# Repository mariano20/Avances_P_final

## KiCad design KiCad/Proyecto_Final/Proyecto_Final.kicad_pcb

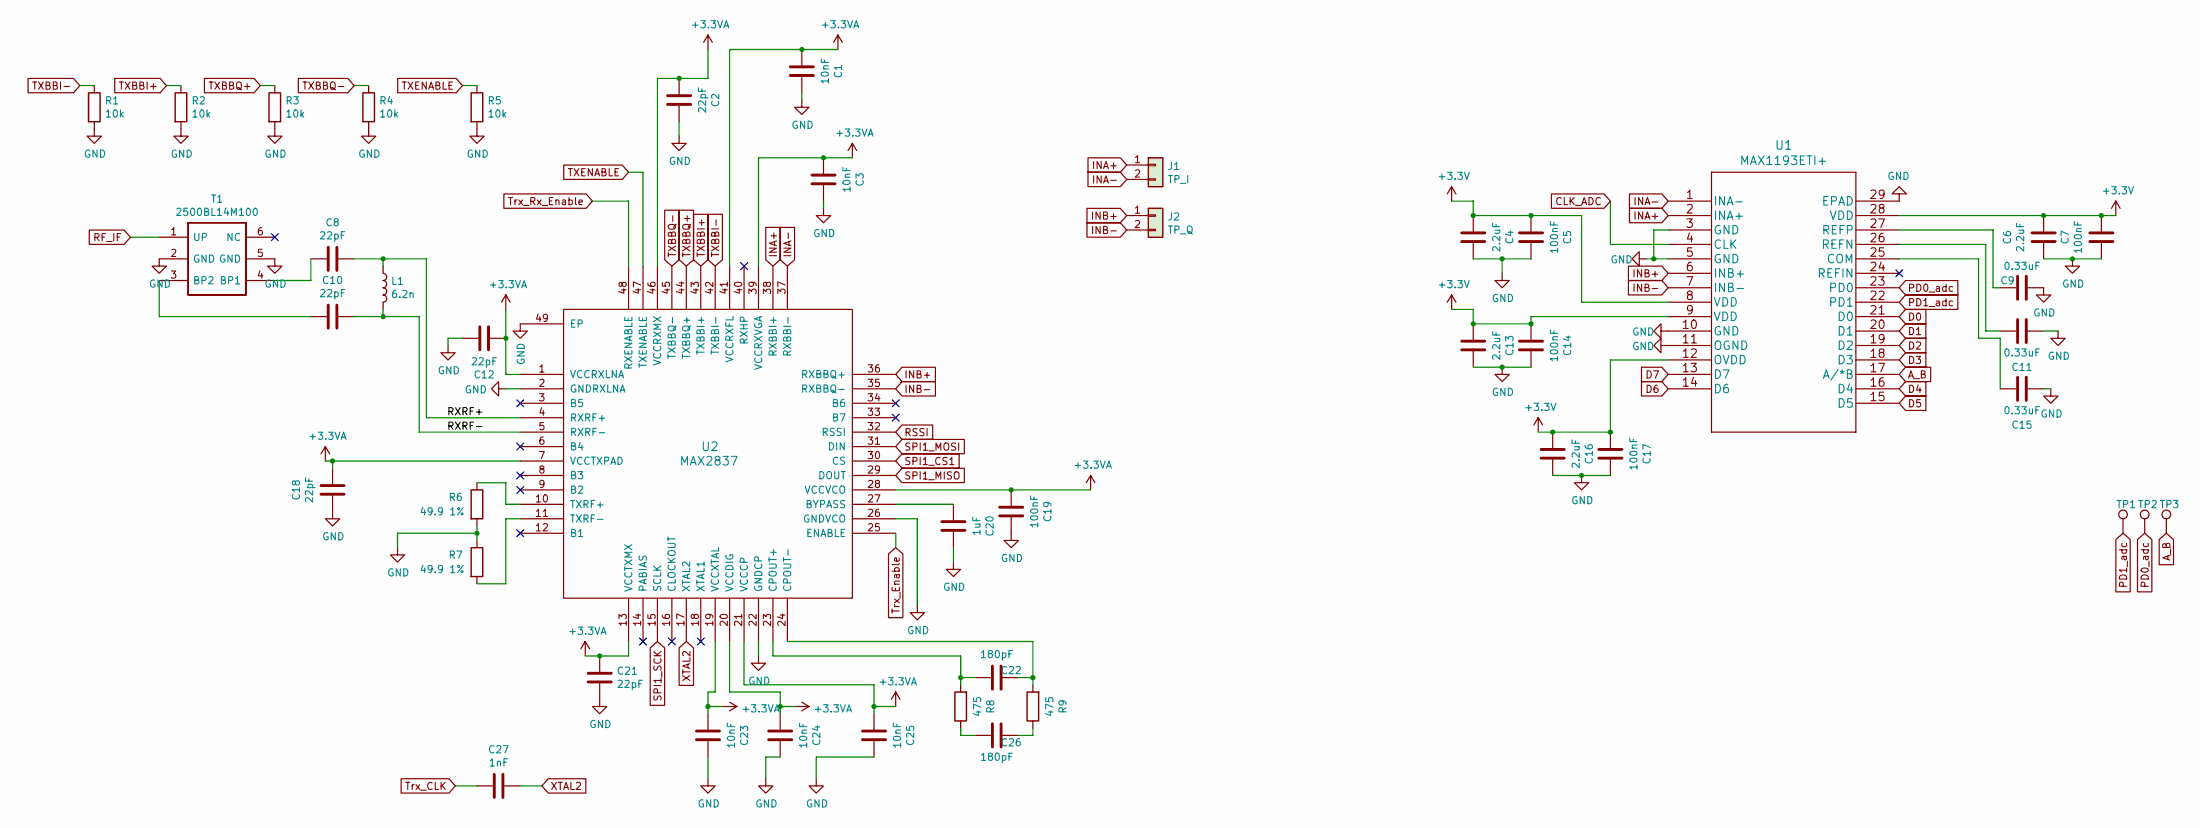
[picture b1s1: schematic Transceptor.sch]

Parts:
C1, C3, C23, C24, C25: 10nF; C_0402_1005Metric
C2, C8, C10, C12, C18, C21: 22pF; C_0402_1005Metric
C4: 2.2uF; C_0603_1608Metric
C5, C7, C14, C17, C19: 100nF; C_0402_1005Metric
C6, C13, C16: 2.2uF; C_0805_2012Metric
C9, C11, C15: 0.33uF; C_0603_1608Metric
C20: 1uF; C_0805_2012Metric
C22, C26: 180pF; C_0402_1005Metric
C27: 1nF; C_0402_1005Metric
J1: TP_I; PinHeader_1x02_P1.27mm_Vertical
J2: TP_Q; PinHeader_1x02_P1.27mm_Vertical
L1: 6.2n; L_0402_1005Metric
R1, R2, R3, R4, R5: 10k; R_0402_1005Metric
R6, R7: 49.9 1%; R_0402_1005Metric
R8, R9: 475; R_0402_1005Metric
T1: 2500BL14M100; Balun_Johanson_1.6x0.8mm; Manufacturer_Part_Number 2500BL14M100T; Mouser Part Number 609-2500BL14M100T
TP1, TP2, TP3: TestPoint; TestPoint_Mask_D0.4mm
U1: MAX1193ETI+; MAX1193ETI&plus_T
U2: MAX2837; MAX2837ETM&plus_

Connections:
+3.3VA: C1.2, C2.2, C3.2, C12.2, C18.1, C19.2, C21.1, C23.2, C24.2, C25.2, U2.1 (VCCRXLNA), U2.7 (VCCTXPAD), U2.13 (VCCTXMX), U2.19 (VCCXTAL), U2.20 (VCCDIG), U2.21 (VCCCP), U2.28 (VCCVCO), U2.39 (VCCRXVGA), U2.41 (VCCRXFL), U2.46 (VCCRXMX); also elsewhere on the board
+3V3: C4.2, C5.2, C6.1, C7.1, C13.2, C14.2, C16.2, C17.2, U1.8 (VDD), U1.9 (VDD), U1.12 (OVDD), U1.28 (VDD); also elsewhere on the board
/Transceptor/RXRF+: C8.1, L1.1, U2.4 (RXRF+)
/Transceptor/RXRF-: C10.1, L1.2, U2.5 (RXRF-)
A_B: TP3.1, U1.17 (A/*B); also elsewhere on the board
CLK_ADC: U1.4 (CLK); also elsewhere on the board
D0: U1.21 (D0); also elsewhere on the board
D1: U1.20 (D1); also elsewhere on the board
D2: U1.19 (D2); also elsewhere on the board
D3: U1.18 (D3); also elsewhere on the board
D4: U1.16 (D4); also elsewhere on the board
D5: U1.15 (D5); also elsewhere on the board
D6: U1.14 (D6); also elsewhere on the board
D7: U1.13 (D7); also elsewhere on the board
GND: C1.1, C2.1, C3.1, C4.1, C5.1, C6.2, C7.2, C9.2, C11.1, C12.1, C13.1, C14.1, C15.1, C16.1, C17.1, C18.2, C19.1, C20.1, C21.2, C23.1, C24.1, C25.1, R1.2, R2.2, R3.2, R4.2, R5.2, R6.2, R7.1, T1.2 (GND), T1.5 (GND), U1.3 (GND), U1.5 (GND), U1.10 (GND), U1.11 (OGND), U1.29 (EPAD), U2.2 (GNDRXLNA), U2.22 (GNDCP), U2.26 (GNDVCO), U2.49 (EP); also elsewhere on the board
INA+: J1.1, U1.2 (INA+), U2.38 (RXBBI+)
INA-: J1.2, U1.1 (INA-), U2.37 (RXBBI-)
INB+: J2.1, U1.6 (INB+), U2.36 (RXBBQ+)
INB-: J2.2, U1.7 (INB-), U2.35 (RXBBQ-)
unnamed: C8.2, T1.4 (BP1)
unnamed: C9.1, U1.27 (REFP)
unnamed: C10.2, T1.3 (BP2)
unnamed: C11.2, U1.26 (REFN)
unnamed: C15.2, U1.25 (COM)
unnamed: C20.2, U2.27 (BYPASS)
unnamed: C22.1, R9.2, U2.24 (CPOUT-)
unnamed: C22.2, R8.2, U2.23 (CPOUT+)
unnamed: C26.1, R9.1
unnamed: C26.2, R8.1
unnamed: R6.1, U2.10 (TXRF+)
unnamed: R7.2, U2.11 (TXRF-)
PD0_adc: TP2.1, U1.23 (PD0); also elsewhere on the board
PD1_adc: TP1.1, U1.22 (PD1); also elsewhere on the board
RF_IF: T1.1 (UP); also elsewhere on the board
RSSI: U2.32 (RSSI); also elsewhere on the board
SPI1_CS1: U2.30 (CS); also elsewhere on the board
SPI1_MISO: U2.29 (DOUT); also elsewhere on the board
SPI1_MOSI: U2.31 (DIN); also elsewhere on the board
SPI1_SCK: U2.15 (SCLK); also elsewhere on the board
TXBBI+: R2.1, U2.43 (TXBBI+)
TXBBI-: R1.1, U2.42 (TXBBI-)
TXBBQ+: R3.1, U2.44 (TXBBQ+)
TXBBQ-: R4.1, U2.45 (TXBBQ-)
TXENABLE: R5.1, U2.47 (TXENABLE)
Trx_CLK: C27.2; also elsewhere on the board
Trx_Enable: U2.25 (ENABLE); also elsewhere on the board
Trx_Rx_Enable: U2.48 (RXENABLE); also elsewhere on the board
XTAL2: C27.1, U2.17 (XTAL2)

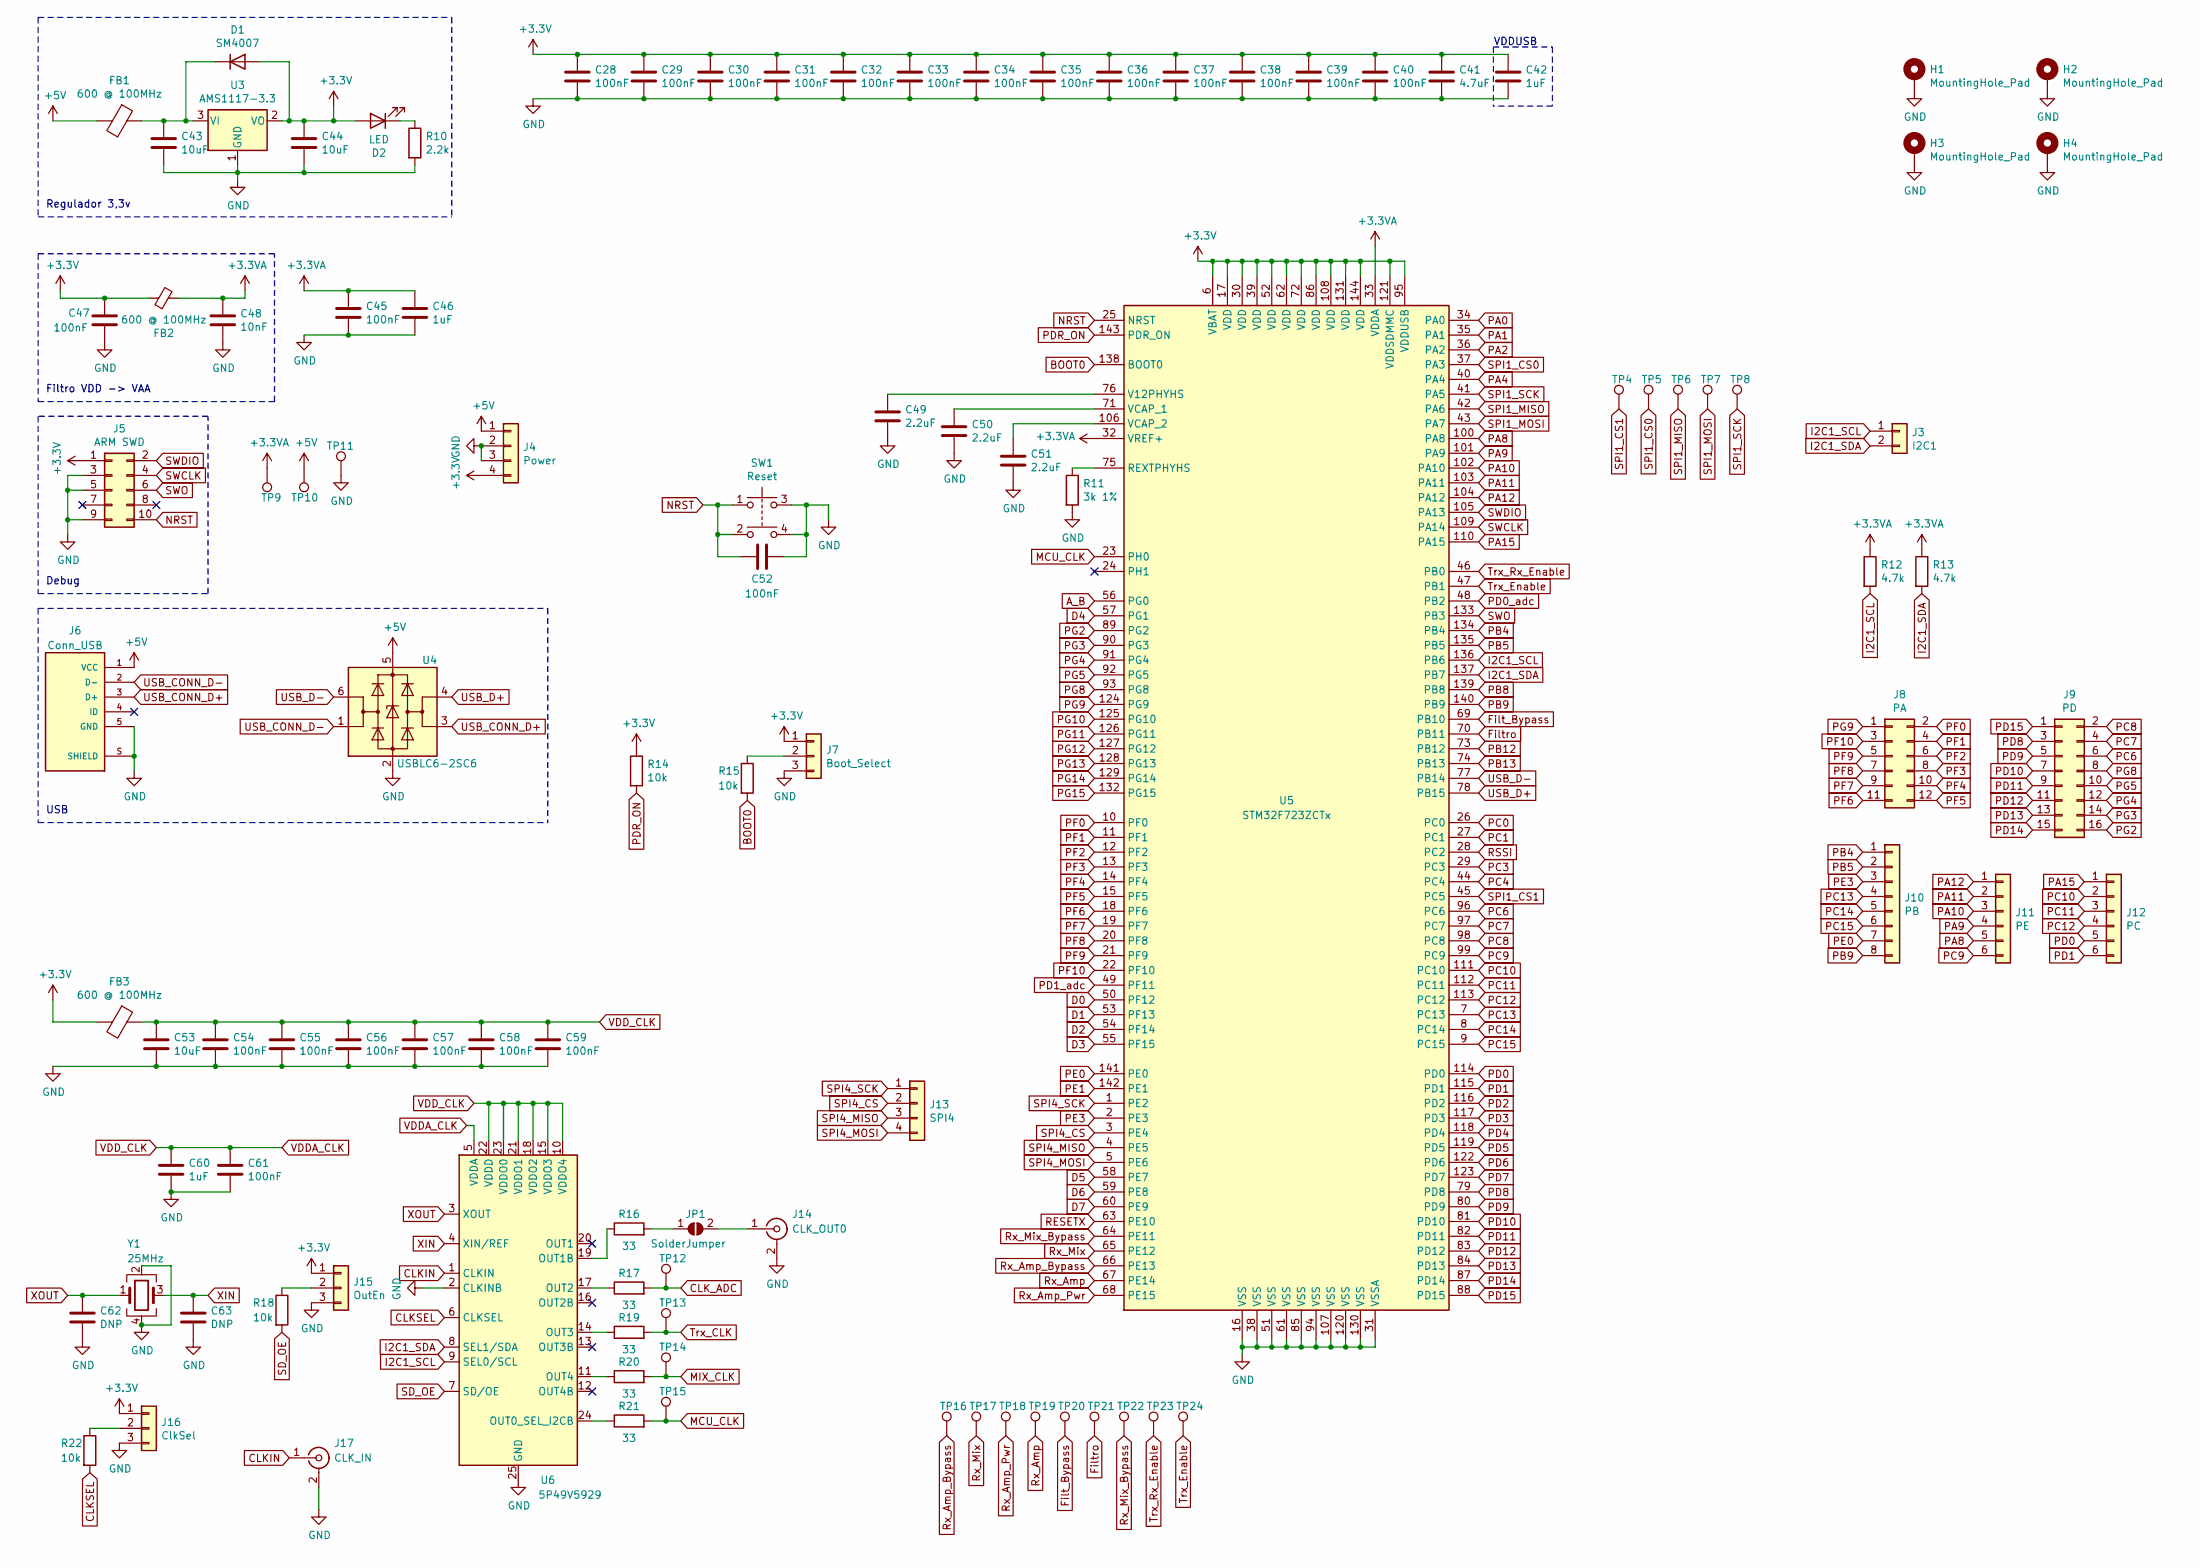
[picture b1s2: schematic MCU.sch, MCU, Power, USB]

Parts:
C28, C29, C30, C31, C32, C33, C34, C35, C36, C37, C38, C39, C40, C45, C47, C52, C54, C55, C56, C57, C58, C59, C61: 100nF; C_0402_1005Metric
C41: 4.7uF; C_0805_2012Metric
C42, C46, C60: 1uF; C_0805_2012Metric
C43, C44, C53: 10uF; C_0805_2012Metric
C48: 10nF; C_0402_1005Metric
C49, C50, C51: 2.2uF; C_0805_2012Metric
C62, C63: DNP; C_0402_1005Metric
D1: SM4007; D_SOD-123F
D2: LED; LED_0603_1608Metric
FB1, FB2, FB3: 600 @ 100MHz; L_0402_1005Metric
H1, H2, H3, H4: MountingHole_Pad; MountingHole_3.2mm_M3_Pad_Via
J3: I2C1; PinHeader_2x01_P2.54mm_Vertical
J4: Power; PinHeader_1x04_P2.54mm_Vertical
J5: ARM SWD; PinHeader_2x05_P2.54mm_Vertical_SMD
J6: Conn_USB; CUI_UJ2-MIBH-G-SMT-TR; PARTREV 1.0
J7: Boot_Select; PinHeader_1x03_P2.54mm_Vertical
J8: PA; PinHeader_2x06_P2.54mm_Vertical
J9: PD; PinHeader_2x08_P2.54mm_Vertical
J10: PB; PinHeader_1x08_P2.54mm_Vertical
J11: PE; PinHeader_1x06_P2.54mm_Vertical
J12: PC; PinHeader_1x06_P2.54mm_Vertical
J13: SPI4; PinHeader_1x04_P2.54mm_Vertical
J14: CLK_OUT0; RFSOLUTIONS_CON-SMA-EDGE-S
J15: OutEn; PinHeader_1x03_P2.54mm_Vertical
J16: ClkSel; PinHeader_1x03_P2.54mm_Vertical
J17: CLK_IN; RFSOLUTIONS_CON-SMA-EDGE-S
JP1: SolderJumper; SolderJumper-2_P1.3mm_Open_RoundedPad1.0x1.5mm
R10: 2.2k; R_0402_1005Metric
R11: 3k 1%; R_0402_1005Metric
R12, R13: 4.7k; R_0402_1005Metric
R14, R15, R18, R22: 10k; R_0402_1005Metric
R16, R17, R19, R20, R21: 33; R_0402_1005Metric
SW1: Reset; PTS647SN50SMTR2LFS
TP4, TP5, TP6, TP7, TP8, TP9, TP10, TP12, TP13, TP14, TP15, TP16, TP17, TP18, TP19, TP20, TP21, TP22, TP23, TP24: TestPoint; TestPoint_Pad_D1.0mm_NoRef
TP11: TestPoint; TestPoint_Pad_1.5x1.5mm
U3: AMS1117-3.3; SOT-223-3_TabPin2
U4: USBLC6-2SC6; SOT-23-6
U5: STM32F723ZCTx; LQFP-144_20x20mm_P0.5mm
U6: 5P49V5929; QFN-24-1EP_4x4mm_P0.5mm_EP2.8x2.8mm
Y1: 25MHz; Crystal_SMD_EuroQuartz_MT-4Pin_3.2x2.5mm

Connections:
+3.3VA: C45.1, C46.1, C48.1, FB2.2, R12.1, R13.1, TP9.1, U5.32 (VREF+), U5.33 (VDDA); also elsewhere on the board
+3V3: C28.1, C29.1, C30.1, C31.1, C32.1, C33.1, C34.1, C35.1, C36.1, C37.1, C38.1, C39.1, C40.1, C41.1, C42.1, C44.1, C47.1, D1.2 (A), D2.2 (A), FB2.1, FB3.2, J4.4, J5.1, J7.1, J15.1, J16.1, R14.1, U3.2 (VO), U5.6 (VBAT), U5.17 (VDD), U5.30 (VDD), U5.39 (VDD), U5.52 (VDD), U5.62 (VDD), U5.72 (VDD), U5.86 (VDD), U5.95 (VDDUSB), U5.108 (VDD), U5.121 (VDDSDMMC), U5.131 (VDD), U5.144 (VDD); also elsewhere on the board
+5V: FB1.2, J4.1, J6.1 (VCC), TP10.1, U4.5 (VBUS)
A_B: U5.56 (PG0); also elsewhere on the board
BOOT0: R15.2, U5.138 (BOOT0)
CLKIN: J17.1 (In), U6.1 (CLKIN)
CLKSEL: R22.2, U6.6 (CLKSEL)
CLK_ADC: R17.2, TP12.1; also elsewhere on the board
D0: U5.50 (PF12); also elsewhere on the board
D1: U5.53 (PF13); also elsewhere on the board
D2: U5.54 (PF14); also elsewhere on the board
D3: U5.55 (PF15); also elsewhere on the board
D4: U5.57 (PG1); also elsewhere on the board
D5: U5.58 (PE7); also elsewhere on the board
D6: U5.59 (PE8); also elsewhere on the board
D7: U5.60 (PE9); also elsewhere on the board
Filt_Bypass: TP20.1, U5.69 (PB10); also elsewhere on the board
Filtro: TP21.1, U5.70 (PB11); also elsewhere on the board
GND: C28.2, C29.2, C30.2, C31.2, C32.2, C33.2, C34.2, C35.2, C36.2, C37.2, C38.2, C39.2, C40.2, C41.2, C42.2, C43.2, C44.2, C45.2, C46.2, C47.2, C48.2, C49.2, C50.2, C51.2, C52.1, C53.2, C54.2, C55.2, C56.2, C57.2, C58.2, C59.2, C60.2, C61.2, C62.2, C63.2, H1.1, H2.1, H3.1, H4.1, J4.2, J4.3, J5.3, J5.5, J5.9, J6.5 (GND), J6.S (SHIELD), J7.3, J14.2 (Ext), J15.3, J16.3, J17.2 (Ext), R10.2, R11.2, SW1.3, SW1.4, TP11.1, U3.1 (GND), U4.2 (GND), U5.16 (VSS), U5.31 (VSSA), U5.38 (VSS), U5.51 (VSS), U5.61 (VSS), U5.85 (VSS), U5.94 (VSS), U5.107 (VSS), U5.120 (VSS), U5.130 (VSS), U6.2 (CLKINB), U6.25 (GND), Y1.2, Y1.4; also elsewhere on the board
I2C1_SCL: J3.1, R12.2, U5.136 (PB6), U6.9 (SEL0/SCL)
I2C1_SDA: J3.2, R13.2, U5.137 (PB7), U6.8 (SEL1/SDA)
MCU_CLK: R21.2, TP15.1, U5.23 (PH0)
MIX_CLK: R20.2, TP14.1; also elsewhere on the board
NRST: C52.2, J5.10, SW1.1, SW1.2, U5.25 (NRST)
unnamed: C43.1, D1.1 (K), FB1.1, U3.3 (VI)
unnamed: C49.1, U5.76 (V12PHYHS)
unnamed: C50.1, U5.71 (VCAP_1)
unnamed: C51.1, U5.106 (VCAP_2)
unnamed: D2.1 (K), R10.1
unnamed: J7.2, R15.1
unnamed: J14.1 (In), JP1.2 (B)
unnamed: J15.2, R18.1
unnamed: J16.2, R22.1
unnamed: JP1.1 (A), R16.2
unnamed: R11.1, U5.75 (REXTPHYHS)
unnamed: R16.1, U6.19 (OUT1B)
unnamed: R17.1, U6.17 (OUT2)
unnamed: R19.1, U6.14 (OUT3)
unnamed: R20.1, U6.11 (OUT4)
unnamed: R21.1, U6.24 (OUT0_SEL_I2CB)
PA0: U5.34 (PA0)
PA1: U5.35 (PA1)
PA2: U5.36 (PA2)
PA4: U5.40 (PA4)
PA8: J11.5, U5.100 (PA8)
PA9: J11.4, U5.101 (PA9)
PA10: J11.3, U5.102 (PA10)
PA11: J11.2, U5.103 (PA11)
PA12: J11.1, U5.104 (PA12)
PA15: J12.1, U5.110 (PA15)
PB4: J10.1, U5.134 (PB4)
PB5: J10.2, U5.135 (PB5)
PB8: U5.139 (PB8)
PB9: J10.8, U5.140 (PB9)
PB12: U5.73 (PB12)
PB13: U5.74 (PB13)
PC0: U5.26 (PC0)
PC1: U5.27 (PC1)
PC3: U5.29 (PC3)
PC4: U5.44 (PC4)
PC6: J9.6, U5.96 (PC6)
PC7: J9.4, U5.97 (PC7)
PC8: J9.2, U5.98 (PC8)
PC9: J11.6, U5.99 (PC9)
PC10: J12.2, U5.111 (PC10)
PC11: J12.3, U5.112 (PC11)
PC12: J12.4, U5.113 (PC12)
PC13: J10.4, U5.7 (PC13)
PC14: J10.5, U5.8 (PC14)
PC15: J10.6, U5.9 (PC15)
PD0: J12.5, U5.114 (PD0)
PD0_adc: U5.48 (PB2); also elsewhere on the board
PD1: J12.6, U5.115 (PD1)
PD1_adc: U5.49 (PF11); also elsewhere on the board
PD2: U5.116 (PD2)
PD3: U5.117 (PD3)
PD4: U5.118 (PD4)
PD5: U5.119 (PD5)
PD6: U5.122 (PD6)
PD7: U5.123 (PD7)
PD8: J9.3, U5.79 (PD8)
PD9: J9.5, U5.80 (PD9)
PD10: J9.7, U5.81 (PD10)
PD11: J9.9, U5.82 (PD11)
PD12: J9.11, U5.83 (PD12)
PD13: J9.13, U5.84 (PD13)
PD14: J9.15, U5.87 (PD14)
PD15: J9.1, U5.88 (PD15)
PDR_ON: R14.2, U5.143 (PDR_ON)
PE0: J10.7, U5.141 (PE0)
PE1: U5.142 (PE1)
PE3: J10.3, U5.2 (PE3)
PF0: J8.2, U5.10 (PF0)
PF1: J8.4, U5.11 (PF1)
PF2: J8.6, U5.12 (PF2)
PF3: J8.8, U5.13 (PF3)
PF4: J8.10, U5.14 (PF4)
PF5: J8.12, U5.15 (PF5)
PF6: J8.11, U5.18 (PF6)
PF7: J8.9, U5.19 (PF7)
PF8: J8.7, U5.20 (PF8)
PF9: J8.5, U5.21 (PF9)
PF10: J8.3, U5.22 (PF10)
PG2: J9.16, U5.89 (PG2)
PG3: J9.14, U5.90 (PG3)
PG4: J9.12, U5.91 (PG4)
PG5: J9.10, U5.92 (PG5)
PG8: J9.8, U5.93 (PG8)
PG9: J8.1, U5.124 (PG9)
PG10: U5.125 (PG10)
PG11: U5.126 (PG11)
PG12: U5.127 (PG12)
PG13: U5.128 (PG13)
PG14: U5.129 (PG14)
PG15: U5.132 (PG15)
RESETX: U5.63 (PE10); also elsewhere on the board
RSSI: U5.28 (PC2); also elsewhere on the board
Rx_Amp: TP19.1, U5.67 (PE14); also elsewhere on the board
Rx_Amp_Bypass: TP16.1, U5.66 (PE13); also elsewhere on the board
Rx_Amp_Pwr: TP18.1, U5.68 (PE15); also elsewhere on the board
Rx_Mix: TP17.1, U5.65 (PE12); also elsewhere on the board
Rx_Mix_Bypass: TP22.1, U5.64 (PE11); also elsewhere on the board
SD_OE: R18.2, U6.7 (SD/OE)
SPI1_CS0: TP5.1, U5.37 (PA3); also elsewhere on the board
SPI1_CS1: TP4.1, U5.45 (PC5); also elsewhere on the board
SPI1_MISO: TP6.1, U5.42 (PA6); also elsewhere on the board
SPI1_MOSI: TP7.1, U5.43 (PA7); also elsewhere on the board
SPI1_SCK: TP8.1, U5.41 (PA5); also elsewhere on the board
SPI4_CS: J13.2, U5.3 (PE4)
SPI4_MISO: J13.3, U5.4 (PE5)
SPI4_MOSI: J13.4, U5.5 (PE6)
SPI4_SCK: J13.1, U5.1 (PE2)
SWCLK: J5.4, U5.109 (PA14)
SWDIO: J5.2, U5.105 (PA13)
SWO: J5.6, U5.133 (PB3)
Trx_CLK: R19.2, TP13.1; also elsewhere on the board
Trx_Enable: TP24.1, U5.47 (PB1); also elsewhere on the board
Trx_Rx_Enable: TP23.1, U5.46 (PB0); also elsewhere on the board
USB_CONN_D+: J6.3 (D+), U4.3 (I/O2)
USB_CONN_D-: J6.2 (D-), U4.1 (I/O1)
USB_D+: U4.4 (I/O2), U5.78 (PB15)
USB_D-: U4.6 (I/O1), U5.77 (PB14)
VDDA_CLK: C53.1, C54.1, C55.1, C56.1, C57.1, C58.1, C59.1, C60.1, C61.1, FB3.1, U6.5 (VDDA), U6.10 (VDDO4), U6.15 (VDDO3), U6.18 (VDDO2), U6.21 (VDDO1), U6.22 (VDDD), U6.23 (VDDO0)
XIN: C63.1, U6.4 (XIN/REF), Y1.3
XOUT: C62.1, U6.3 (XOUT), Y1.1

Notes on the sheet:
Regulador 3,3v
Filtro VDD -> VAA
Debug
USB
VDDUSB

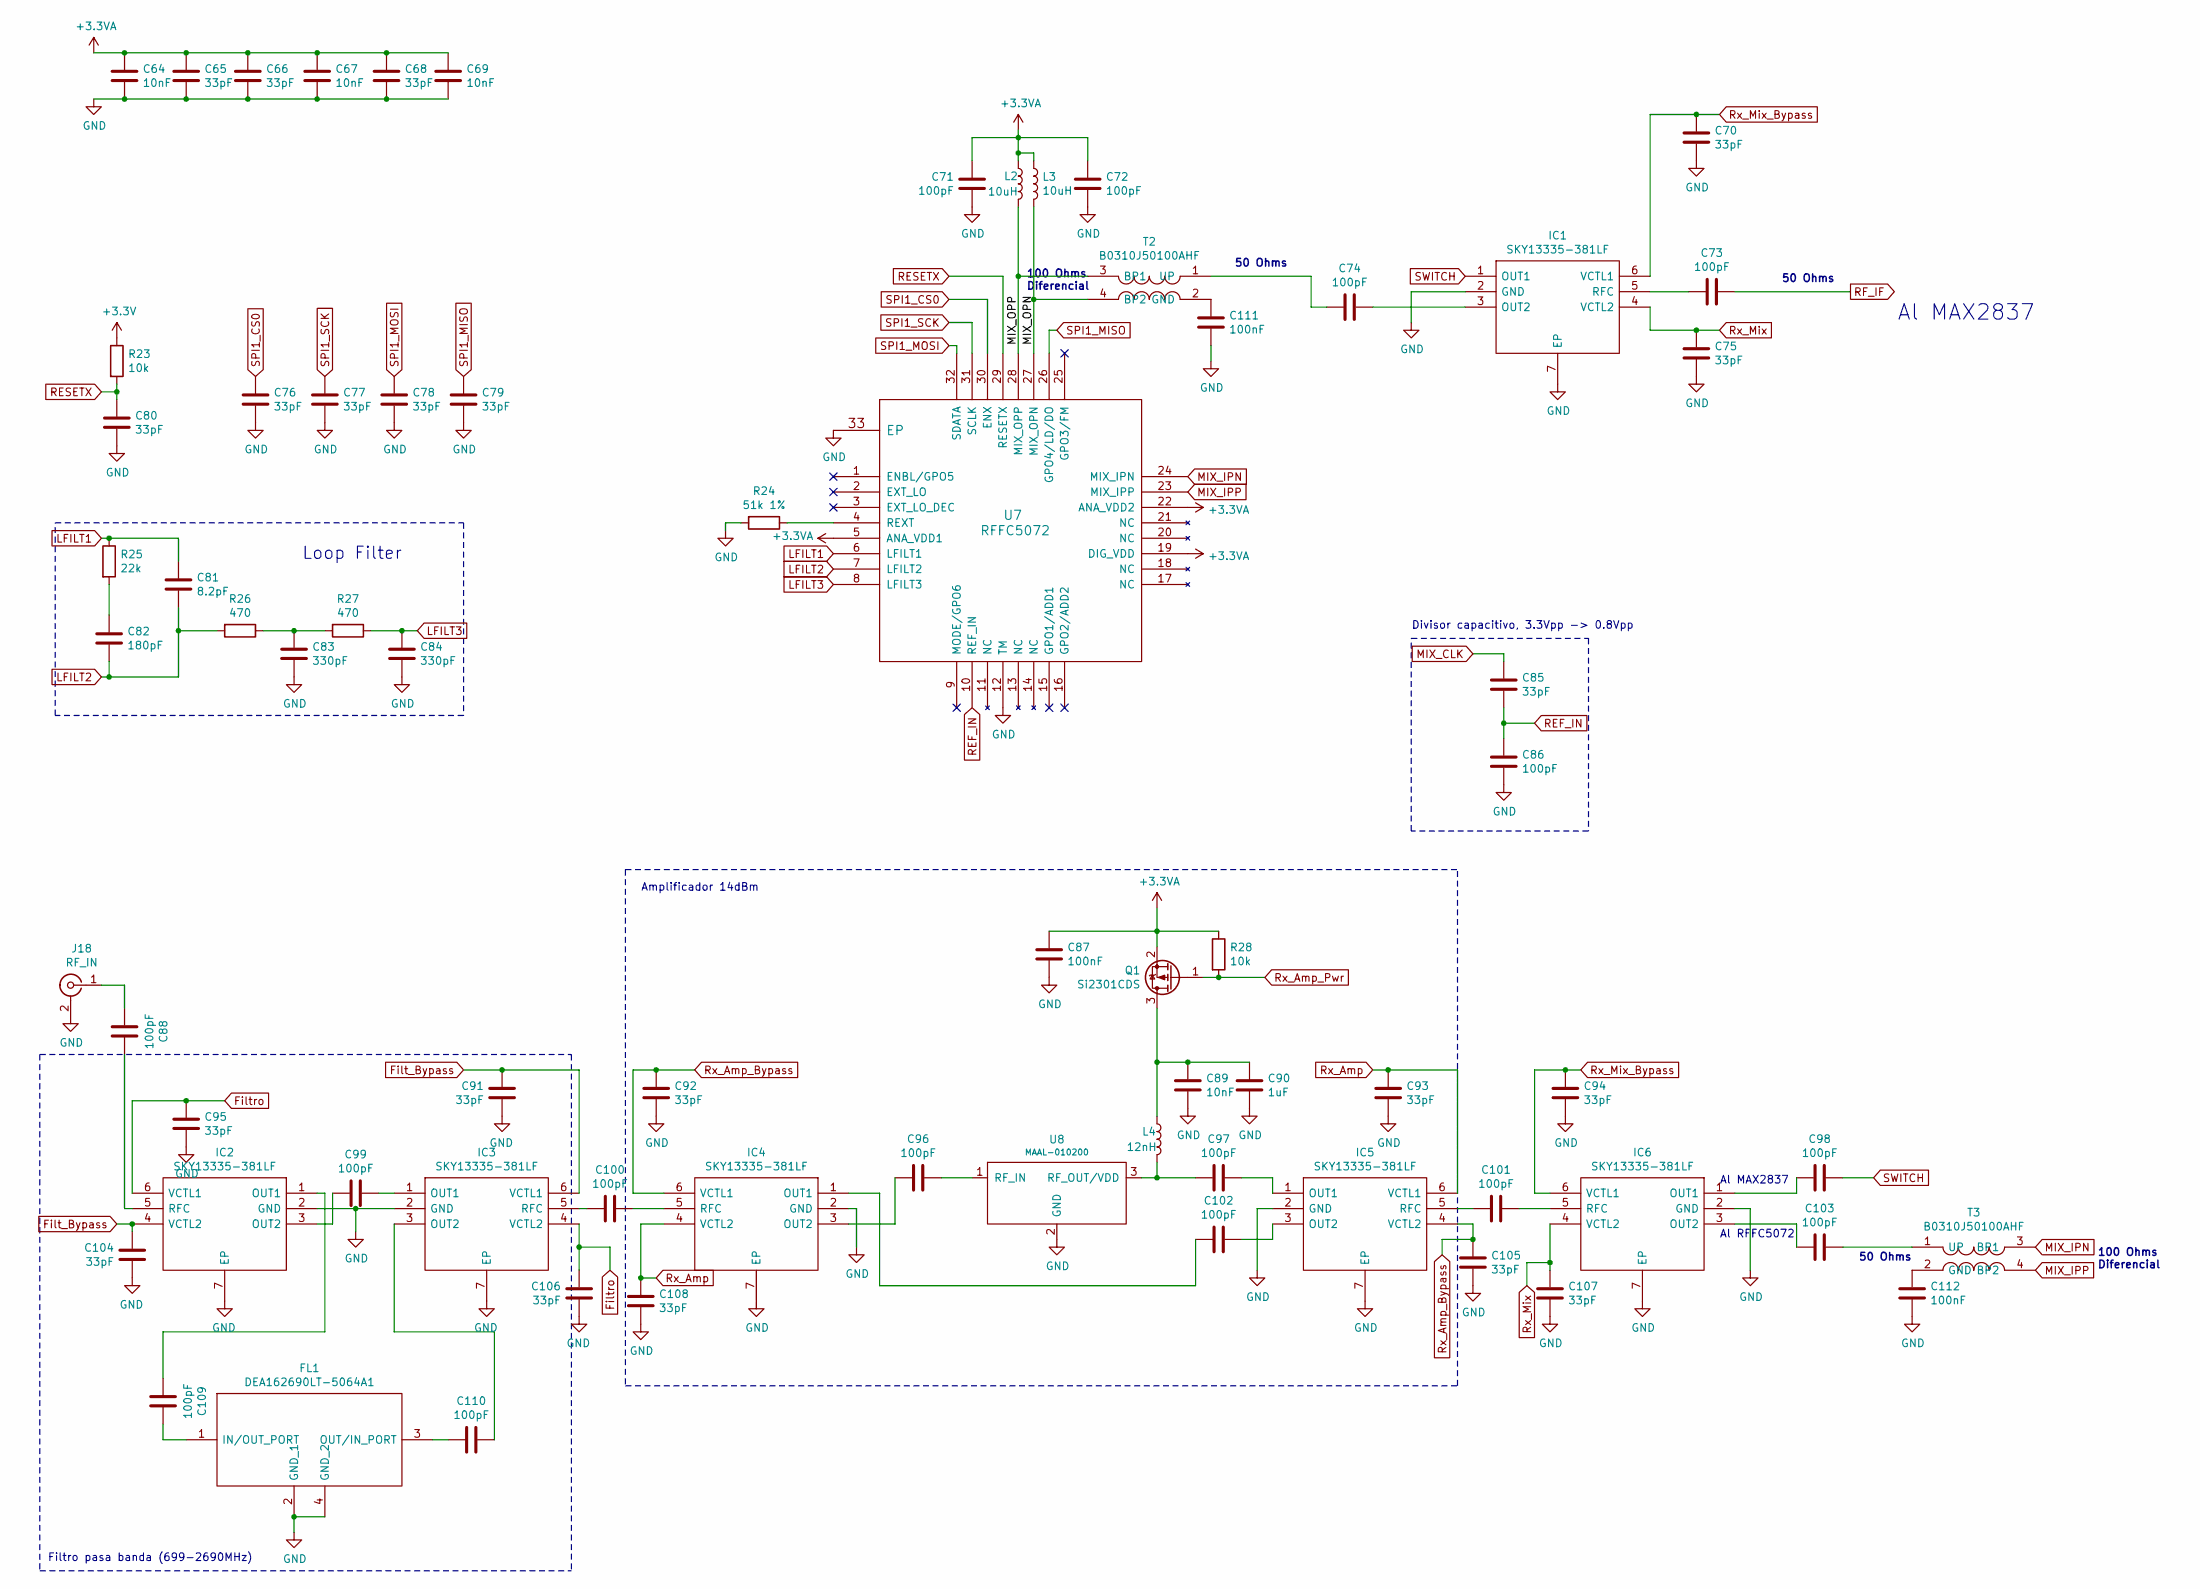
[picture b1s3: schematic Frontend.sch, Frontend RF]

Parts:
C64, C67, C69, C89: 10nF; C_0402_1005Metric
C65, C66, C68, C70, C75, C76, C77, C78, C79, C80, C85, C91, C92, C93, C94, C95, C104, C105, C106, C107, C108: 33pF; C_0402_1005Metric
C71, C72, C73, C74, C86, C88, C96, C97, C98, C99, C100, C101, C102, C103, C109, C110: 100pF; C_0402_1005Metric
C81: 8.2pF; C_0603_1608Metric
C82: 180pF; C_0201_0603Metric
C83, C84: 330pF; C_0402_1005Metric
C87, C111, C112: 100nF; C_0402_1005Metric
C90: 1uF; C_0402_1005Metric
FL1: DEA162690LT-5064A1; DEA162690LT5051B1; Manufacturer_Part_Number DEA162690LT-5064A1
IC1, IC2, IC3, IC4, IC5, IC6: SKY13335-381LF; SON50P200X150X50-7N; Mouser Part Number 873-SKY13335-381LF
J18: RF_IN; RFSOLUTIONS_CON-SMA-EDGE-S
L2, L3: 10uH; L_0805_2012Metric
L4: 12nH; L_0402_1005Metric
Q1: Si2301CDS; SOT-23
R23, R28: 10k; R_0402_1005Metric
R24: 51k 1%; R_0402_1005Metric
R25: 22k; R_0402_1005Metric
R26, R27: 470; R_0402_1005Metric
T2, T3: B0310J50100AHF; Manufacturer_Part_Number B0310J50100AHF; Mouser Part Number 620-B0310J50100AHF
U7: RFFC5072; QFN-32-1EP_5x5mm_P0.5mm_EP3.7x3.7mm
U8: MAAL-010200; SOT-89-3

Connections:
+3.3VA: C64.1, C65.1, C66.1, C67.1, C68.1, C69.1, C71.1, C72.1, C87.1, L2.1, L3.1, Q1.2 (S), R28.1, U7.5 (ANA_VDD1), U7.19 (DIG_VDD), U7.22 (ANA_VDD2); also elsewhere on the board
+3V3: R23.1; also elsewhere on the board
/Frontend_analog/MIX_OPN: L3.2, T2.4 (BP2), U7.27 (MIX_OPN)
/Frontend_analog/MIX_OPP: L2.2, T2.3 (BP1), U7.28 (MIX_OPP)
Filt_Bypass: C91.1, C104.1, IC2.4 (VCTL2), IC3.6 (VCTL1); also elsewhere on the board
Filtro: C95.1, C106.1, IC2.6 (VCTL1), IC3.4 (VCTL2); also elsewhere on the board
GND: C64.2, C65.2, C66.2, C67.2, C68.2, C69.2, C70.2, C71.2, C72.2, C75.2, C76.2, C77.2, C78.2, C79.2, C80.2, C83.2, C84.2, C86.2, C87.2, C89.2, C90.2, C91.2, C92.2, C93.2, C94.2, C95.2, C104.2, C105.2, C106.2, C107.2, C108.2, C111.2, C112.2, FL1.2 (GND_1), FL1.4 (GND_2), IC1.2 (GND), IC1.7 (EP), IC2.2 (GND), IC2.7 (EP), IC3.2 (GND), IC3.7 (EP), IC4.2 (GND), IC4.7 (EP), IC5.2 (GND), IC5.7 (EP), IC6.2 (GND), IC6.7 (EP), J18.2 (Ext), R24.2, U7.12 (TM), U7.33 (EP), U8.2 (GND); also elsewhere on the board
LFILT1: C81.1, R25.1, U7.6 (LFILT1)
LFILT2: C81.2, C82.2, R26.2, U7.7 (LFILT2)
LFILT3: C84.1, R27.1, U7.8 (LFILT3)
MIX_CLK: C85.1; also elsewhere on the board
MIX_IPN: T3.3 (BP1), U7.24 (MIX_IPN)
MIX_IPP: T3.4 (BP2), U7.23 (MIX_IPP)
unnamed: C73.2, IC1.5 (RFC)
unnamed: C74.1, IC1.3 (OUT2)
unnamed: C74.2, T2.1 (UP)
unnamed: C82.1, R25.2
unnamed: C83.1, R26.1, R27.2
unnamed: C88.1, IC2.5 (RFC)
unnamed: C88.2, J18.1 (In)
unnamed: C89.1, C90.1, L4.1, Q1.3 (D)
unnamed: C96.1, U8.1 (RF_IN)
unnamed: C96.2, IC4.3 (OUT2)
unnamed: C97.1, IC5.1 (OUT1)
unnamed: C97.2, L4.2, U8.3 (RF_OUT/VDD)
unnamed: C98.2, IC6.1 (OUT1)
unnamed: C99.1, IC3.1 (OUT1)
unnamed: C99.2, IC2.3 (OUT2)
unnamed: C100.1, IC4.5 (RFC)
unnamed: C100.2, IC3.5 (RFC)
unnamed: C101.1, IC6.5 (RFC)
unnamed: C101.2, IC5.5 (RFC)
unnamed: C102.1, IC5.3 (OUT2)
unnamed: C102.2, IC4.1 (OUT1)
unnamed: C103.1, T3.1 (UP)
unnamed: C103.2, IC6.3 (OUT2)
unnamed: C109.1, FL1.1 (IN/OUT_PORT)
unnamed: C109.2, IC2.1 (OUT1)
unnamed: C110.1, IC3.3 (OUT2)
unnamed: C110.2, FL1.3 (OUT/IN_PORT)
unnamed: C111.1, T2.2 (GND)
unnamed: C112.1, T3.2 (GND)
unnamed: R24.1, U7.4 (REXT)
REF_IN: C85.2, C86.1, U7.10 (REF_IN)
RESETX: C80.1, R23.2, U7.29 (RESETX); also elsewhere on the board
RF_IF: C73.1; also elsewhere on the board
Rx_Amp: C93.1, C108.1, IC4.4 (VCTL2), IC5.6 (VCTL1); also elsewhere on the board
Rx_Amp_Bypass: C92.1, C105.1, IC4.6 (VCTL1), IC5.4 (VCTL2); also elsewhere on the board
Rx_Amp_Pwr: Q1.1 (G), R28.2; also elsewhere on the board
Rx_Mix: C75.1, C107.1, IC1.4 (VCTL2), IC6.4 (VCTL2); also elsewhere on the board
Rx_Mix_Bypass: C70.1, C94.1, IC1.6 (VCTL1), IC6.6 (VCTL1); also elsewhere on the board
SPI1_CS0: C76.1, U7.30 (ENX); also elsewhere on the board
SPI1_MISO: C79.1, U7.26 (GPO4/LD/DO); also elsewhere on the board
SPI1_MOSI: C78.1, U7.32 (SDATA); also elsewhere on the board
SPI1_SCK: C77.1, U7.31 (SCLK); also elsewhere on the board
SWITCH: C98.1, IC1.1 (OUT1)

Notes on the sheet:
Loop Filter
50 Ohms
Al MAX2837
Al RFFC5072
100 Ohms Diferencial
Filtro pasa banda (699-2690MHz)
Amplificador 14dBm
Divisor capacitivo, 3.3Vpp -> 0.8Vpp

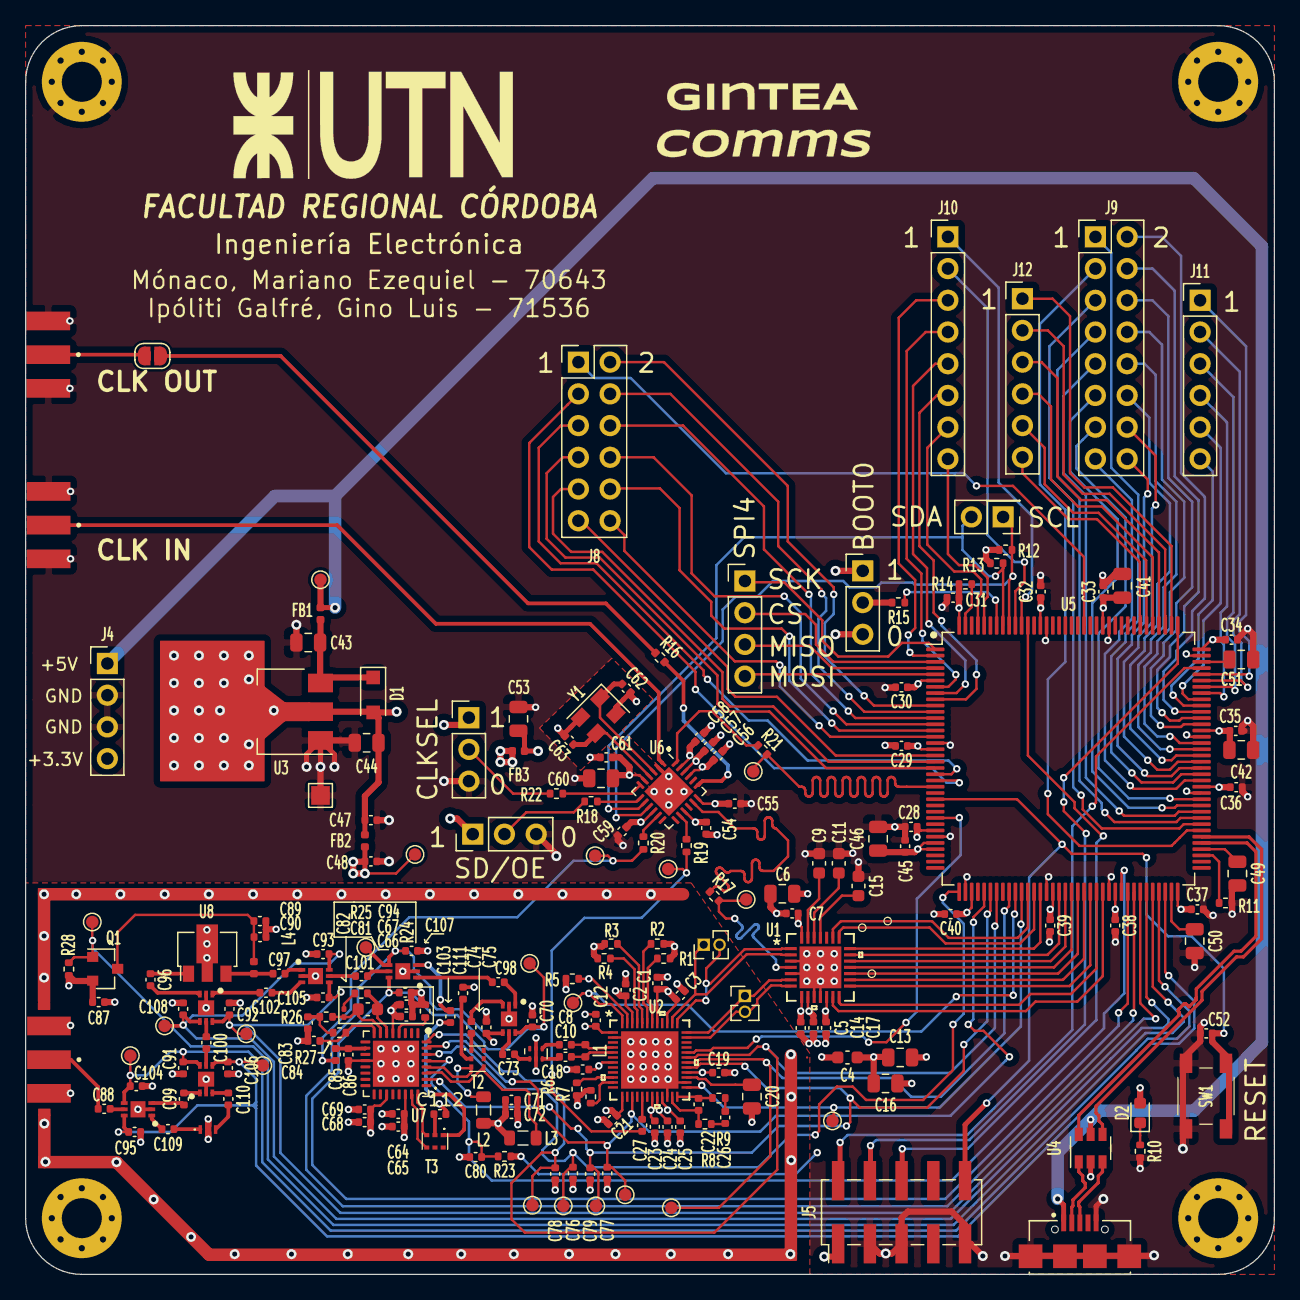
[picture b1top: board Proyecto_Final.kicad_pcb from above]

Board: 4 copper layers, 100.0 x 100.0 mm, 217 parts (0 on the bottom side), 185 nets.

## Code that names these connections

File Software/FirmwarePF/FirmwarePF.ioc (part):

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PH0-OSC_IN.Signal=RCC_OSC_IN
PE11.GPIOParameters=GPIO_Label
PG4.Signal=GPIO_Output
PG8.Signal=GPIO_Output
PC12.Signal=GPIO_Output
PG0.Signal=GPIO_Input
PA3.GPIOParameters=GPIO_Speed,PinState,GPIO_Label
PA3.GPIO_Speed=GPIO_SPEED_FREQ_VERY_HIGH
PB13.Signal=GPIO_Output
PG13.Signal=GPIO_Output
RCC.SYSCLKSource=RCC_SYSCLKSOURCE_PLLCLK
PF7.Signal=GPIO_Output
PE2.Mode=Full_Duplex_Master
PD4.Signal=GPIO_Output
PB6.Signal=I2C1_SCL
PC7.Signal=GPIO_Output
PB6.Mode=I2C
PC3.Signal=GPIO_Output
PD0.Signal=GPIO_Output
PD8.Signal=GPIO_Output
PE5.Signal=SPI4_MISO
PE1.Signal=GPIO_Output
PB2.Signal=GPIO_Output
PB3.Mode=Trace_Asynchronous_SW
PG1.GPIOParameters=GPIO_Label
PF12.GPIO_Label=D0
PB0.GPIOParameters=GPIO_Label
PE9.Signal=GPIO_Input
PB14.Mode=Internal_Phy_Device
PB1.GPIO_Label=Trx_Enable
PE4.GPIO_Label=SPI4_CS
PE2.Signal=SPI4_SCK
PA8.Signal=GPIO_Output
PF3.Signal=GPIO_Output
PE10.Signal=GPIO_Output
Mcu.Package=LQFP144
PB9.Signal=GPIO_Output
PB1.Signal=GPIO_Output
PE10.GPIOParameters=GPIO_Label
PD12.Signal=GPIO_Output
PA10.Signal=GPIO_Output
PE12.GPIO_Label=Rx_Mix
PF14.Signal=GPIO_Input
PB10.GPIOParameters=GPIO_Label
PE10.GPIO_Label=RESETX
PD15.Signal=GPIO_Output
PA5.Mode=Full_Duplex_Master
PG12.Signal=GPIO_Output
PG5.Signal=GPIO_Output
PG9.Signal=GPIO_Output
PC13.Signal=GPIO_Output
PD3.Signal=GPIO_Output
PC2.Signal=ADCx_IN12
PC6.Signal=GPIO_Output
PB11.GPIO_Label=Filtro
PD7.Signal=GPIO_Output
PD1.Signal=GPIO_Output
PF14.GPIO_Label=D2
PC0.Signal=GPIO_Output
PC14-OSC32_IN.Signal=GPIO_Output
PF13.GPIO_Label=D1
PA0-WKUP.Signal=GPIO_Output
PG10.Signal=GPIO_Output
PD10.Signal=GPIO_Output
PE8.GPIO_Label=D6
PA9.Signal=GPIO_Output
PB11.GPIOParameters=GPIO_Label
PE9.GPIO_Label=D7
PB10.Signal=GPIO_Output
PB14.Signal=USB_OTG_HS_DM
PA5.Signal=SPI1_SCK
PE13.GPIOParameters=GPIO_Label
PE14.Signal=GPIO_Output
PE6.Mode=Full_Duplex_Master
PE15.Signal=GPIO_Output
PE8.Signal=GPIO_Input
PC2.GPIOParameters=GPIO_Label
PF13.Signal=GPIO_Input
PA13.Mode=Trace_Asynchronous_SW
PA4.Signal=GPIO_Output
PB5.Signal=GPIO_Output
PE13.GPIO_Label=Rx_Amp_Bypass
PD11.Signal=GPIO_Output
PA11.Signal=GPIO_Output
PF9.Signal=GPIO_Output
PC5.GPIO_Speed=GPIO_SPEED_FREQ_VERY_HIGH
PG0.GPIOParameters=GPIO_Label
PE3.Signal=GPIO_Output
PE4.PinState=GPIO_PIN_SET
PA3.PinState=GPIO_PIN_SET
PF4.Signal=GPIO_Output
PE12.GPIOParameters=GPIO_Label
PD2.Signal=GPIO_Output
PB0.Signal=GPIO_Output
PC1.Signal=GPIO_Output
PA6.Mode=Full_Duplex_Master
Mcu.UserName=STM32F723ZCTx
PG2.Signal=GPIO_Output
PE11.GPIO_Label=Rx_Mix_Bypass
PC10.Signal=GPIO_Output
PB0.GPIO_Label=Trx_Rx_Enable
PB11.Signal=GPIO_Output
PB15.Signal=USB_OTG_HS_DP
PF12.GPIOParameters=GPIO_Label
PG11.Signal=GPIO_Output
PG15.Signal=GPIO_Output
PD13.Signal=GPIO_Output
PA12.Signal=GPIO_Output
PE4.GPIOParameters=GPIO_Speed,PinState,GPIO_Label
PF11.GPIO_Label=PD1_adc
PF12.Signal=GPIO_Input
PH0-OSC_IN.Mode=HSE-External-Clock-Source
RCC.HSE_VALUE=25000000
PE13.Signal=GPIO_Output
PA14.Mode=Trace_Asynchronous_SW
PE4.GPIO_Speed=GPIO_SPEED_FREQ_VERY_HIGH
PF11.Signal=GPIO_Output
PB7.Signal=I2C1_SDA
PF11.GPIOParameters=GPIO_Label
PE4.Signal=GPIO_Output
PH1-OSC_OUT.Mode=HSE-External-Clock-Source
PA6.Signal=SPI1_MISO
PA15.Signal=GPIO_Output
PF8.Signal=GPIO_Output
PG0.GPIO_Label=A_B
PF5.Signal=GPIO_Output
PF0.Signal=GPIO_Output
PC5.Signal=GPIO_Output
PE7.Signal=GPIO_Input
PD6.Signal=GPIO_Output
PF15.GPIOParameters=GPIO_Label
PC2.GPIO_Label=RSSI
PB4.Signal=GPIO_Output
PA3.Signal=GPIO_Output
PE8.GPIOParameters=GPIO_Label
PA7.Mode=Full_Duplex_Master
PE14.GPIOParameters=GPIO_Label
PG3.Signal=GPIO_Output
PG1.Signal=GPIO_Input
PC11.Signal=GPIO_Output
PC8.Signal=GPIO_Output
PC4.Signal=GPIO_Output
PE14.GPIO_Label=Rx_Amp
PD9.Signal=GPIO_Output
PD5.Signal=GPIO_Output
PE9.GPIOParameters=GPIO_Label
PE15.GPIOParameters=GPIO_Label
PA13.Signal=SYS_JTMS-SWDIO
PE15.GPIO_Label=Rx_Amp_Pwr
PF6.Signal=GPIO_Output
PB10.GPIO_Label=Filt_Bypass
PE7.GPIOParameters=GPIO_Label
PC5.GPIOParameters=GPIO_Speed,PinState,GPIO_Label
PB2.GPIOParameters=GPIO_Label
PF2.Signal=GPIO_Output
PE11.Signal=GPIO_Output
PC15-OSC32_OUT.Signal=GPIO_Output
PA1.Signal=GPIO_Output
PG14.Signal=GPIO_Output
board=custom
PG1.GPIO_Label=D4
PF14.GPIOParameters=GPIO_Label
PB15.Mode=Internal_Phy_Device
PF10.Signal=GPIO_Output
PE5.Mode=Full_Duplex_Master
PH1-OSC_OUT.Signal=RCC_OSC_OUT
PF15.GPIO_Label=D3
PF15.Signal=GPIO_Input
PF1.Signal=GPIO_Output
PE6.Signal=SPI4_MOSI
Mcu.Name=STM32F723Z(C-E)Tx
PE0.Signal=GPIO_Output
PE7.GPIO_Label=D5
PE12.Signal=GPIO_Output
PA2.Signal=GPIO_Output
PD14.Signal=GPIO_Output
PB3.Signal=SYS_JTDO-SWO
RCC.SYSCLKFreq_VALUE=216000000
PC5.PinState=GPIO_PIN_SET
PC5.GPIO_Label=SPI1_CS1
PB7.Mode=I2C
PA14.Signal=SYS_JTCK-SWCLK
PB2.GPIO_Label=PD0_adc
PF13.GPIOParameters=GPIO_Label
PB8.Signal=GPIO_Output
PC9.Signal=GPIO_Output
PB12.Signal=GPIO_Output
PA3.GPIO_Label=SPI1_CS0
PB1.GPIOParameters=GPIO_Label
PA7.Signal=SPI1_MOSI

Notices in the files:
parts and their libraries:
Copyright 2016 Accelerated Designs. All rights reserved.
